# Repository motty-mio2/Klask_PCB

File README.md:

# Klask PCB

This repository contains the KiCad project files for **Klask PCB**, a custom Arduino Uno R3 shield designed to control stepper motors and limit switches for manipulating a **Klask** board game.

## Overview

**Klask PCB** is a hardware interface designed to automate or robotize the board game "Klask". It uses stepper motors to move the game magnets under the board. 

The shield drives two stepper motors (X and Y axes) using Pololu-style DRV8825 stepper driver modules and processes signals from homing limit switches to align the axes. Additionally, it integrates a power sense circuit to detect external 12V supply and is powered efficiently via a USB-PD Trigger Module.

---

## Features

- **Dual Axis Control**: Supports two DRV8825 stepper motor driver modules for X and Y axes.
- **Homing Support**: Hardware inputs for X and Y axis limit switches to perform auto-calibration (0-point homing).
- **USB-PD Powered**: Powered via an external 12V supply using a USB-PD Trigger Module.
- **Power Detection (Power Sense)**: Built-in voltage divider and noise-filtering circuit to safely detect whether the 12V motor power supply is active using the Arduino `D10` pin.
- **Visual Indicator**: LED indicator to show the status of the 12V power supply.
- **Minimalist Arduino Shield**: Uses only the Digital headers (10-pin and 8-pin) of the Arduino Uno R3 to minimize interference and pin usage.

---

## Bill of Materials (BOM)

Below is the list of components required to assemble the Klask PCB.

| Component | Designator | Qty | Description / Footprint |
| --- | --- | --- | --- |
| **DRV8825 Stepper Driver Module** | A1, A2 | 2 | Pololu Breakout board style stepper driver |
| **Arduino UNO R3** | A3 | 1 | Microcontroller board (acts as base) |
| **USB-PD Trigger Module** | — | 1 | Set to 12V output mode |
| **10-pin Pin Header** | — | 1 | 2.54mm pitch (for Arduino Digital High header) |
| **8-pin Pin Header** | — | 1 | 2.54mm pitch (for Arduino Digital Low header) |
| **8-pin Pin Socket** | — | 4 | 2.54mm pitch (sockets for DRV8825 modules) |
| **LED** | D1 | 1 | 3mm THT LED (Power/12V Status Indicator) |
| **2.54mm Terminal Block** | J1, J2, J3, J4, J5, SW4, SW5 | 7 | XY308-2.54-2P (For MotXA, MotXB, MotYA, MotYB, 12V, SWX, SWY) |
| **510 Ω Resistor** | R1 | 1 | THT Resistor (LED current limiting) |
| **180 Ω Resistor** | R2 | 1 | THT Resistor (Power sensing voltage divider) |
| **0.1 µF Capacitor** | C1 | 1 | Ceramic Capacitor THT (Power sense noise filter) |
| **100 µF Capacitor** | C3, C4 | 2 | Electrolytic Capacitor THT (Motor power decoupling) |

*Note: SW2 (SW_A) and SW3 (SW_B) are present on the PCB layout for potential UI expansion but are not populated in this build.*

---

## Pin Mapping

The Arduino Uno R3 digital pins are mapped to the stepper drivers, limit switches, and power sense circuit as follows:

### Stepper Motor Drivers (DRV8825)
| Signal Name | Arduino Uno Pin | DRV8825 Pin | Description |
| --- | --- | --- | --- |
| `/MX_STEP` | `D8` | `STEP` (A1) | X-axis step control pulse |
| `/MX_DIR` | `D9` | `DIR` (A1) | X-axis rotation direction |
| `/MY_STEP` | `D4` | `STEP` (A2) | Y-axis step control pulse |
| `/MY_DIR` | `D5` | `DIR` (A2) | Y-axis rotation direction |
| `/nEN` | `D3` | `~{RST}`, `~{SLP}` (A1, A2) | Driver enable (Reset / Sleep control) |
| `/M0` | `D0 / RX` | `M0` (A1, A2) | Microstep configuration bit 0 |
| `/M1` | `D1 / TX` | `M1` (A1, A2) | Microstep configuration bit 1 |
| `/M2` | `D2` | `M2` (A1, A2) | Microstep configuration bit 2 |

### Limit Switches & Sensors
| Signal Name | Arduino Uno Pin | PCB Connector | Description |
| --- | --- | --- | --- |
| `/SW_X` | `A5` (Digital I/O) | `SW4` | X-axis homing limit switch (Active Low) |
| `/SW_Y` | `A4` (Digital I/O) | `SW5` | Y-axis homing limit switch (Active Low) |
| `GND` | `GND` | `SW4`, `SW5` | Common Ground for switches |

### Power Sense & Feedback
| Signal Name | Arduino Uno Pin | Related Parts | Description |
| --- | --- | --- | --- |
| `/A0` | `D10` | `D1`, `R1`, `R2`, `C1` | Input pin to sense if 12V is connected (HIGH = 12V Present) |

---

## Hardware Connection & Assembly

1. **Terminal Blocks Wiring**:
   - **`J5` (12V Input)**: Connect the 12V and GND outputs from the **USB-PD Trigger Module**.
   - **`J1` & `J2`**: Connect to the X-axis stepper motor coils (Phase A to `J1`, Phase B to `J2`).
   - **`J3` & `J4`**: Connect to the Y-axis stepper motor coils (Phase A to `J3`, Phase B to `J4`).
   - **`SW4` & `SW5`**: Connect to the X-axis and Y-axis limit switches.
2. **Arduino Uno Mounting**:
   - Solder the 10-pin and 8-pin male headers to the digital side of the shield.
   - Solder the power sense circuit parts (`D1`, `R1`, `R2`, `C1`) and decoupling capacitors (`C3`, `C4`).
   - Stack the shield onto the Arduino Uno R3.
3. **Stepper Drivers**:
   - Solder the 8x4 female pin sockets onto the shield.
   - Insert the DRV8825 stepper driver modules into the sockets. Make sure the orientation is correct (VMOT/GND pin alignment).

---

## License

This project is licensed under the **CC BY-SA 4.0** (Creative Commons Attribution-ShareAlike 4.0 International) license. Feel free to share, copy, and modify, provided appropriate credit is given and any derivative works are distributed under the same license.

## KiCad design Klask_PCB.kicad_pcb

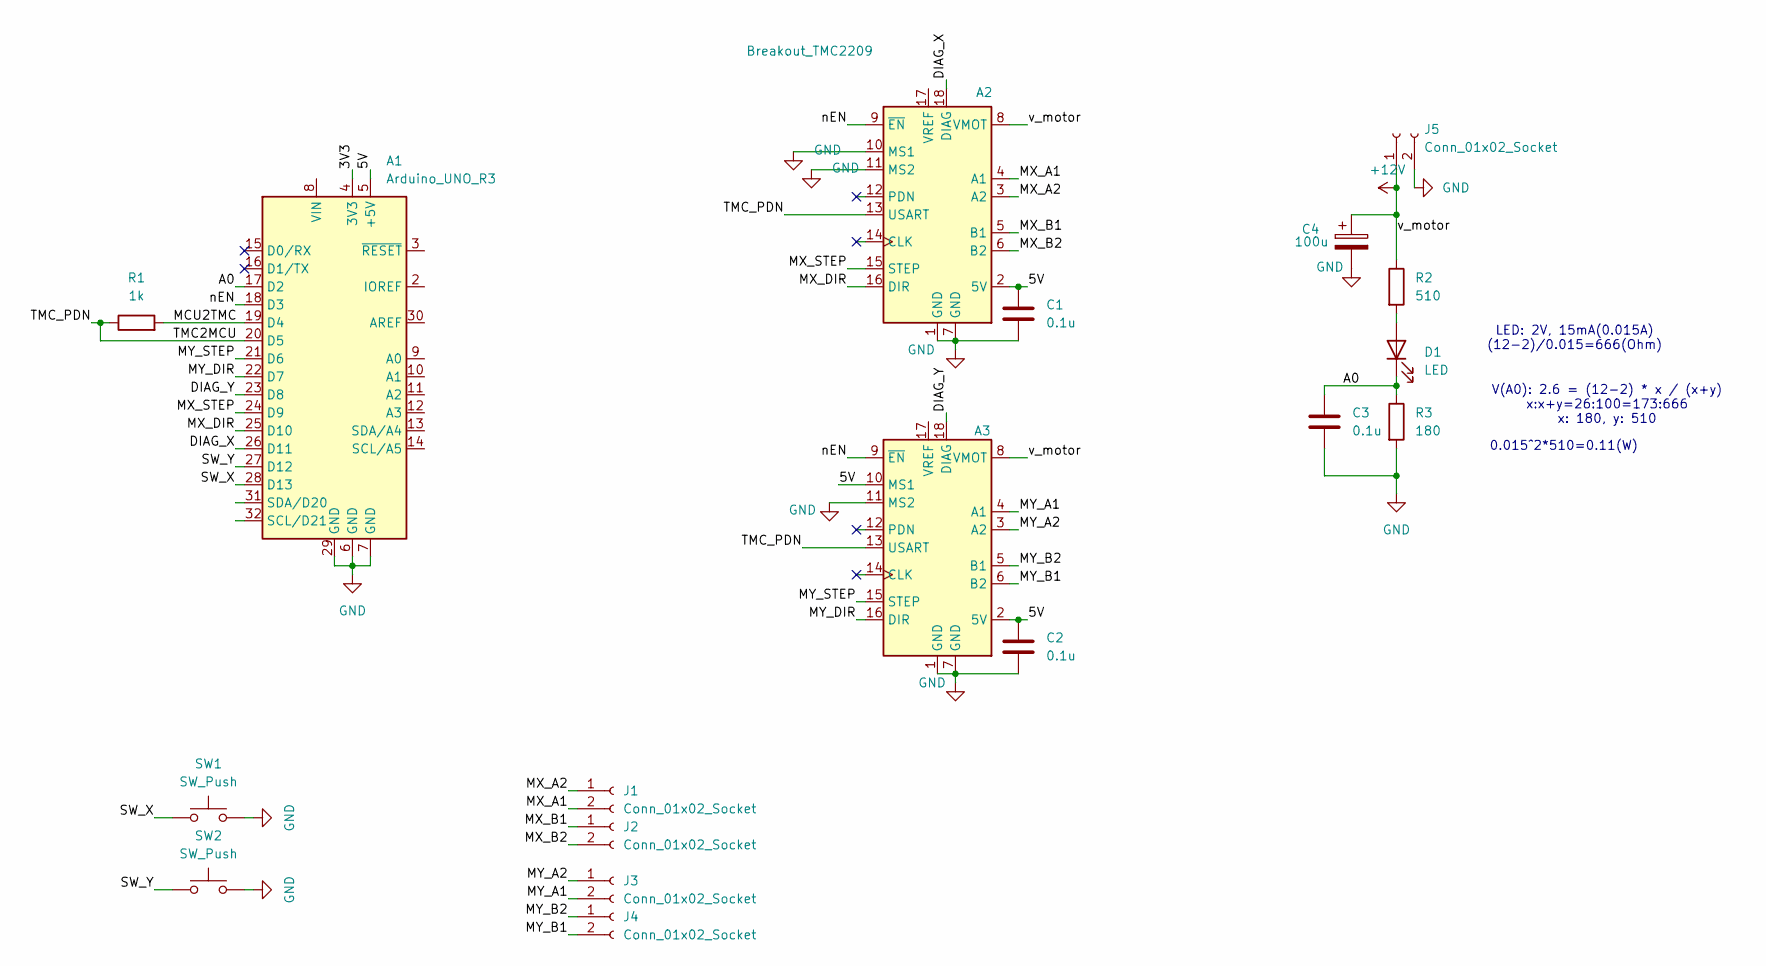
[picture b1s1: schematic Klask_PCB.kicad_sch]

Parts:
A1: Arduino_UNO_R3; Arduino_UNO_Q
A2: Breakout_TMC2209; TMC2209
A3: Pololu_Breakout_DRV8825; TMC2209
C1, C2, C3: 0.1u; C_Axial_L3.8mm_D2.6mm_P7.50mm_Horizontal
C4: 100u; CP_Radial_D5.0mm_P2.50mm
D1: LED; LED_D3.0mm
J1, J2, J3, J4, J5: Conn_01x02_Socket; TerminalBlock_Xinya_XY308-2.54-2P_1x02_P2.54mm_Horizontal
R1: 1k; R_Box_L8.4mm_W2.5mm_P5.08mm
R2: 510; R_Box_L8.4mm_W2.5mm_P5.08mm
R3: 180; R_Box_L8.4mm_W2.5mm_P5.08mm
SW1, SW2: SW_Push; TerminalBlock_Xinya_XY308-2.54-2P_1x02_P2.54mm_Horizontal

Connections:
+12V: A2.8 (VMOT), A3.8 (VMOT), C4.1, J5.1, R2.1
/3V3: A1.4 (3V3)
/5V: A1.5 (+5V), A2.2 (5V), A3.2 (5V), A3.10 (MS1), C1.1, C2.1
/A0: A1.17 (D2), C3.1, D1.1 (K), R3.1
/DIAG_X: A1.26 (D11), A2.18 (DIAG)
/DIAG_Y: A1.23 (D8), A3.18 (DIAG)
/MCU2TMC: A1.19 (D4), R1.2
/MX_A1: A2.4 (A1), J1.2
/MX_A2: A2.3 (A2), J1.1
/MX_B1: A2.5 (B1), J2.1
/MX_B2: A2.6 (B2), J2.2
/MX_DIR: A1.25 (D10), A2.16 (DIR)
/MX_STEP: A1.24 (D9), A2.15 (STEP)
/MY_A1: A3.4 (A1), J3.2
/MY_A2: A3.3 (A2), J3.1
/MY_B1: A3.6 (B2), J4.2
/MY_B2: A3.5 (B1), J4.1
/MY_DIR: A1.22 (D7), A3.16 (DIR)
/MY_STEP: A1.21 (D6), A3.15 (STEP)
/SW_X: A1.28 (D13), SW1.1
/SW_Y: A1.27 (D12), SW2.1
/TMC2MCU: A1.20 (D5), A2.13 (USART), A3.13 (USART), R1.1
/nEN: A1.18 (D3), A2.9 (~EN), A3.9 (~EN)
GND: A1.6 (GND), A1.7 (GND), A1.29 (GND), A2.1 (GND), A2.7 (GND), A2.10 (MS1), A2.11 (MS2), A3.1 (GND), A3.7 (GND), A3.11 (MS2), C1.2, C2.2, C3.2, C4.2, J5.2, R3.2, SW1.2, SW2.2
unnamed: D1.2 (A), R2.2

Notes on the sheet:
LED: 2V, 15mA(0.015A) (12-2)/0.015=666(Ohm)
0.015^2*510=0.11(W)
V(A0): 2.6 = (12-2) * x / (x+y) x:x+y=26:100=173:666 x: 180, y: 510

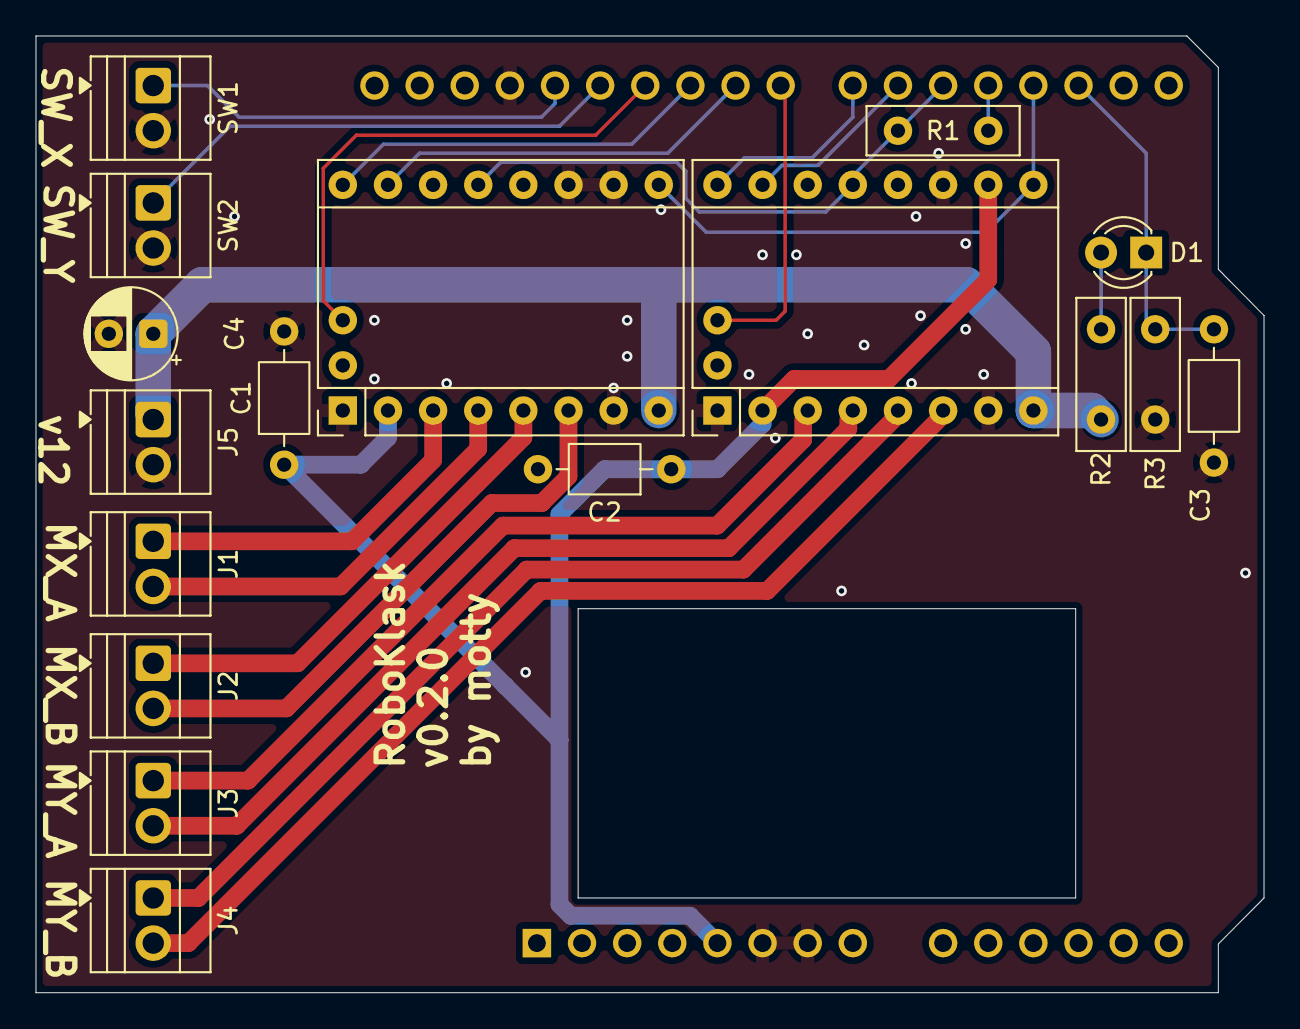
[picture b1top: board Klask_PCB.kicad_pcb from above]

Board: 2 copper layers, 69.1 x 53.8 mm, 18 parts (1 on the bottom side), 24 nets.

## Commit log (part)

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2026-05-17 init
2026-05-30 update ver
